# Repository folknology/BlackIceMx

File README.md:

# BlackIceMx
BlackIceMx - Core Module carrier with MixMods/Pmod interfaces

[Get BlackIce Mx from Tindie](https://www.tindie.com/products/Folknology/blackice-mx/)

Needs to be combined with a Core module, for example [IceCore](https://github.com/folknology/IceCore)

Supports MixMods (in addition to Pmods)

Supports the [BlackEdge connectivity](https://github.com/folknology/BlackEdge) core modules

More [BlackIce Mx background](https://forum.mystorm.uk/t/new-product-blackice-mx/551/10) on the [forum](https://forum.mystorm.uk/)

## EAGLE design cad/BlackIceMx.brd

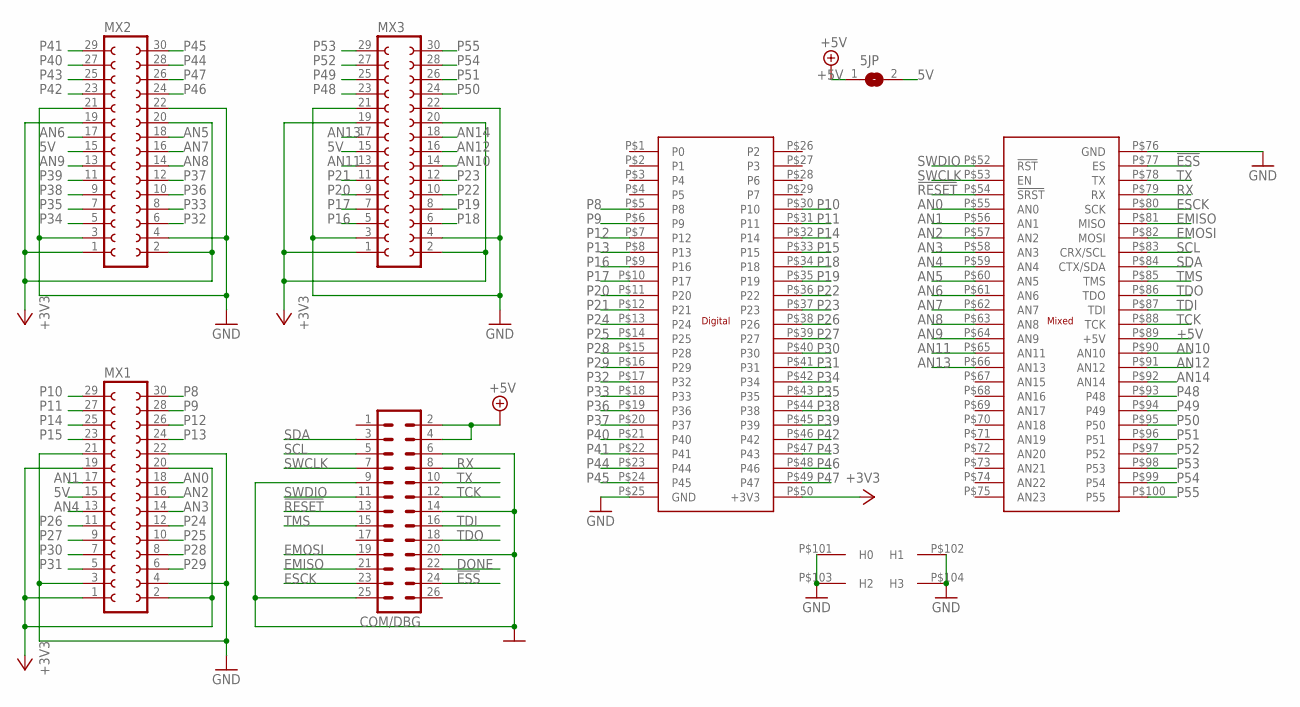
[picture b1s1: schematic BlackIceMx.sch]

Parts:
5JP: SJ
COM/DBG: MA13-2
MX1, MX2, MX3: FE15-2
U$1: BE-CARRIERSMD; BE-CARRIER-SMD

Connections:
5V: 5JP.2, MX1.15, MX2.15, MX3.15
!ESS: COM/DBG.24, U$1.P$77 (ES)
!RESET: COM/DBG.13, U$1.P$54 (!SRST)
+3V3: MX1.1, MX1.2, MX1.19, MX1.20, MX2.1, MX2.2, MX2.19, MX2.20, MX3.1, MX3.2, MX3.19, MX3.20, U$1.P$50 (+3V3)
+5V: 5JP.1, COM/DBG.2, COM/DBG.4, U$1.P$89 (+5V)
AN0: MX1.18, U$1.P$55 (AN0)
AN1: MX1.17, U$1.P$56 (AN1)
AN2: MX1.16, U$1.P$57 (AN2)
AN3: MX1.14, U$1.P$58 (AN3)
AN4: MX1.13, U$1.P$59 (AN4)
AN5: MX2.18, U$1.P$60 (AN5)
AN6: MX2.17, U$1.P$61 (AN6)
AN7: MX2.16, U$1.P$62 (AN7)
AN8: MX2.14, U$1.P$63 (AN8)
AN9: MX2.13, U$1.P$64 (AN9)
AN10: MX3.14, U$1.P$90 (AN10)
AN11: MX3.13, U$1.P$65 (AN11)
AN12: MX3.16, U$1.P$91 (AN12)
AN13: MX3.17, U$1.P$66 (AN13)
AN14: MX3.18, U$1.P$92 (AN14)
DONE: COM/DBG.22
EMISO: COM/DBG.21, U$1.P$81 (MISO)
EMOSI: COM/DBG.19, U$1.P$82 (MOSI)
ESCK: COM/DBG.23, U$1.P$80 (SCK)
GND: COM/DBG.6, COM/DBG.9, COM/DBG.14, COM/DBG.20, COM/DBG.25, MX1.3, MX1.4, MX1.21, MX1.22, MX2.3, MX2.4, MX2.21, MX2.22, MX3.3, MX3.4, MX3.21, MX3.22, U$1.P$25 (GND), U$1.P$76 (GND), U$1.P$101 (H0), U$1.P$102 (H1), U$1.P$103 (H2), U$1.P$104 (H3)
P8: MX1.30, U$1.P$5 (P8)
P9: MX1.28, U$1.P$6 (P9)
P10: MX1.29, U$1.P$30 (P10)
P11: MX1.27, U$1.P$31 (P11)
P12: MX1.26, U$1.P$7 (P12)
P13: MX1.24, U$1.P$8 (P13)
P14: MX1.25, U$1.P$32 (P14)
P15: MX1.23, U$1.P$33 (P15)
P16: MX3.5, U$1.P$9 (P16)
P17: MX3.7, U$1.P$10 (P17)
P18: MX3.6, U$1.P$34 (P18)
P19: MX3.8, U$1.P$35 (P19)
P20: MX3.9, U$1.P$11 (P20)
P21: MX3.11, U$1.P$12 (P21)
P22: MX3.10, U$1.P$36 (P22)
P23: MX3.12, U$1.P$37 (P23)
P24: MX1.12, U$1.P$13 (P24)
P25: MX1.10, U$1.P$14 (P25)
P26: MX1.11, U$1.P$38 (P26)
P27: MX1.9, U$1.P$39 (P27)
P28: MX1.8, U$1.P$15 (P28)
P29: MX1.6, U$1.P$16 (P29)
P30: MX1.7, U$1.P$40 (P30)
P31: MX1.5, U$1.P$41 (P31)
P32: MX2.6, U$1.P$17 (P32)
P33: MX2.8, U$1.P$18 (P33)
P34: MX2.5, U$1.P$42 (P34)
P35: MX2.7, U$1.P$43 (P35)
P36: MX2.10, U$1.P$19 (P36)
P37: MX2.12, U$1.P$20 (P37)
P38: MX2.9, U$1.P$44 (P38)
P39: MX2.11, U$1.P$45 (P39)
P40: MX2.27, U$1.P$21 (P40)
P41: MX2.29, U$1.P$22 (P41)
P42: MX2.23, U$1.P$46 (P42)
P43: MX2.25, U$1.P$47 (P43)
P44: MX2.28, U$1.P$23 (P44)
P45: MX2.30, U$1.P$24 (P45)
P46: MX2.24, U$1.P$48 (P46)
P47: MX2.26, U$1.P$49 (P47)
P48: MX3.23, U$1.P$93 (P48)
P49: MX3.25, U$1.P$94 (P49)
P50: MX3.24, U$1.P$95 (P50)
P51: MX3.26, U$1.P$96 (P51)
P52: MX3.27, U$1.P$97 (P52)
P53: MX3.29, U$1.P$98 (P53)
P54: MX3.28, U$1.P$99 (P54)
P55: MX3.30, U$1.P$100 (P55)
RX: COM/DBG.8, U$1.P$79 (RX)
SCL: COM/DBG.5, U$1.P$83 (CRX/SCL)
SDA: COM/DBG.3, U$1.P$84 (CTX/SDA)
SWCLK: COM/DBG.7, U$1.P$53 (EN)
SWDIO: COM/DBG.11, U$1.P$52 (!RST)
TCK: COM/DBG.12, U$1.P$88 (TCK)
TDI: COM/DBG.16, U$1.P$87 (TDI)
TDO: COM/DBG.18, U$1.P$86 (TDO)
TMS: COM/DBG.15, U$1.P$85 (TMS)
TX: COM/DBG.10, U$1.P$78 (TX)

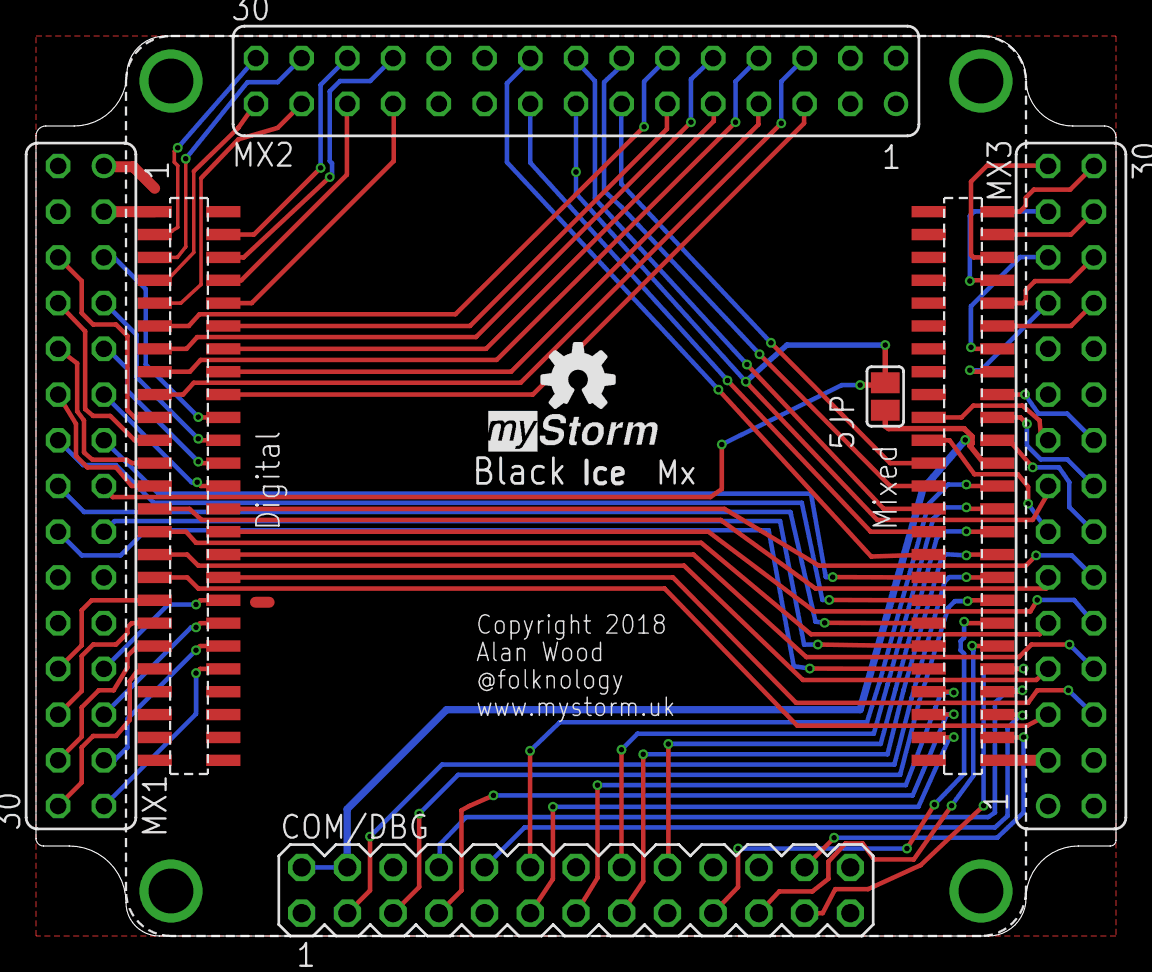
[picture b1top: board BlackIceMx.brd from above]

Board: 2 copper layers, 60.0 x 50.0 mm, 6 parts (0 on the bottom side), 82 nets.

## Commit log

2019-05-18 Added initial BlackIceMx files
2019-06-21 Updated to BlackEdge library
2019-06-21 Updated Layout and schematic files
2019-06-21 Added BlackIce pic
2019-06-21 Updated Schematic pdf
2019-07-03 Updated BlackIce board
2019-07-03 Added loaded board pics
2019-07-03 Updated Readme - ref BlackEdge repo
2019-07-04 Added BlackIce + core image and reverted to carrier jpeg
2019-07-04 Added images into readme page
2019-07-04 Updated readme page
2019-07-04 Renamed fully loaded image
2019-07-10 Added linbk to tindie
2019-09-02 Added Pinout diagram from Ed on forum

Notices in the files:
cad/BlackIceMx.brd:
Copyright 2018
parts and their libraries:
SparkFun-Aesthetics: Licensing: Creative Commons ShareAlike 4.0 International - https://creativecommons.org/licenses/by-sa/4.0
